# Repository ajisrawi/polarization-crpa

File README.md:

# polarization-crpa: 12-element polarization-diverse GNSS anti-jam array

This project studies a 12-channel GNSS CRPA (controlled reception pattern antenna)
that cancels jammers using **polarization and direction together**. It covers the
full chain:
- signal-level anti-jam simulation,
- antenna design checked with openEMS (FDTD),
- KiCad hardware for the antenna boards,
- schematics for the RF front-end, the RFSoC beamformer and the u-blox ZED-X20P receiver.

## Status (read before using anything here)

| Part | State |
|---|---|
| Anti-jam simulator (STAP, power inversion, MVDR, RF-chain mismatch and equalization) | Working, see below |
| **Antenna element rev C** (air-spaced dual-band stacked patch, 4 probes; [hardware/em](hardware/em)) | **openEMS-simulated:** +4.4 to +5.7 dBic at L5/E5/L2/G2/E6 and +7.8 to +8.1 dBic at L1/E1/B1/G1. Axial ratio 0.5-2.2 dB, except E6/B3 at 3.5 dB. |
| Full 12-element array in openEMS | Running / in progress |
| Rev C KiCad boards | Not yet updated (rev A and rev B boards are in `hardware/antenna*`) |
| Rev C active-element, front-end and DSP schematics | Pass ERC; candidate parts marked VERIFY |
| Built or measured hardware | **None.** Everything here is simulation or design data. |

Rev B (`hardware/antenna_tmm`, compact TMM3 ceramic element) was simulated and **rejected**:
its single resonance gives only about 3 % bandwidth, while the lower GNSS block needs 11 %.
The boards are kept for reference.

> **Disclaimer.** This is research and simulation work, not a validated product.
> - Pinouts, footprints and parts marked VERIFY must be checked against the datasheets.
> - The SMD hybrid land pattern is a placeholder.
> - The element must be prototyped and measured before any production.
>
> **Export control.** GNSS anti-jam / CRPA technology is dual-use and controlled in many
> jurisdictions (for example the Wassenaar Arrangement category 7, US EAR/ITAR). Anyone using,
> modifying or shipping these designs is responsible for complying with the export rules
> that apply to them.

- Hardware: [hardware/README.md](hardware/README.md)
- EM models: [hardware/em/em_element.py](hardware/em/em_element.py) (single element) and
  [hardware/em/em_array.py](hardware/em/em_array.py) (full array)
- `run_hardware_array.py` simulates the array exactly as laid out on the plate.
- To install openEMS for the EM scripts:
  1. Download `openEMS_x64_v0.37.0_msvc.zip` from github.com/thliebig/openEMS-Project.
  2. Extract it to `tools/openEMS/`.
  3. Create the Python environment: `uv venv tools/emvenv --python 3.13`.
  4. Install the bundled wheels: `uv pip install --python tools/emvenv/Scripts/python.exe --no-index --find-links tools/openEMS/openEMS/python openEMS`.

## Anti-jam simulator

A simulator for a 12-channel GNSS CRPA. It cancels jammers using **polarization
and direction together** (space-polarization-time adaptive processing, STAP).
Each run synthesizes the raw IQ samples of all 12 channels, runs the adaptive
beamformer on those samples, and scores the result on the true signal model.

```bash
python run_experiments.py
```

Figures and `results/summary.md` are written to `results/`. A full run takes
several minutes, and most of that time is the Monte Carlo in experiment 3.

## Files

| File | Contents |
|---|---|
| `crpa_model.py` | Antenna/port polarization models, array geometry, wideband signal generation, RF-chain mismatch, FIR channel equalizer |
| `crpa_dsp.py` | Space-time snapshots, covariance, power inversion (blind), MVDR (satellite beams), scoring, sky maps |
| `run_experiments.py` | The three array designs and three experiments |

## Arrays compared (12 RF channels each)

| | Design | Elements |
|---|---|---|
| A | Conventional CRPA | 12 RHCP patches, 4x3 grid, lambda/2 spacing |
| B | Your design | 3 RHCP + 3 LHCP + 3 linear "H" patches (0/60/120 deg) + 3 vertical monopoles, same 4x3 grid |
| C | Dual-pol CRPA | 6 dual-feed patches (centre + ring of 5, radius lambda/2), RHCP and LHCP ports both digitized |

## What the model includes

- **Full polarization.** Every port has a direction-dependent receive vector
  (E_theta, E_phi), and every wave has a Jones vector (RHCP satellites; linear,
  circular or elliptical jammers).
- **Physical element patterns.**
  - A patch's E-plane still radiates at grazing angles and its H-plane does not.
    A linear patch is therefore truly "horizontal" only in its H-plane.
  - RHCP patches lose about 12 dB toward the horizon.
  - Monopoles have a null at zenith and their peak at the horizon.
- **Finite cross-polarization isolation** of every port (25 dB by default).
- **Exact wideband array response.** True time delays across the aperture are
  modelled at 10 MS/s complex baseband around L1.
- **RF-chain mismatch** per channel: gain, phase, about 1 ns of delay spread,
  and filter ripple.
- **Channel equalization.** A 64-tap FIR per channel is fitted to a
  calibration-noise injection.
- **Jammer types:** wideband noise jammers (2-8 MHz), CW, and an RHCP "smart" jammer.
- **Satellite C/N0.** In-band jammer power is treated as extra white noise. The
  reference is 45 dB-Hz at 0 dBic, and the tracking threshold is 28 dB-Hz.

## What the model does NOT include

The following are not modelled, so read the results as a comparison between the
designs, not as absolute hardware predictions:

- mutual coupling between elements,
- platform and ground multipath,
- ADC quantization and AGC,
- satellite code and carrier tracking loops (C/N0 is computed analytically),
- errors in attitude and ephemeris.

## Algorithms

- **Power inversion (PI).** Minimizes the output power with unit gain on one
  RHCP reference channel. It is blind: it needs no satellite directions,
  attitude or antenna calibration.
- **MVDR.** Forms one beam per satellite, with unit gain toward that satellite's
  space-polarization steering vector and minimum output power. It needs a
  calibrated array manifold (residual calibration error is modelled at
  0.2 dB / 2 deg), plus attitude and ephemeris.
- Both run as STAP with 1 or 5 taps per channel. A diagonal loading of
  0.1 x noise is applied.

## RHCP jammer study (`python run_rhcp_jammer.py`)

A SkyShield-type GNSS jammer transmits RHCP. This study tests tilting
elements toward the jammer (`Port.boresight_el_deg` / `boresight_az_deg`).
Results are in `results/rhcp_summary.md`.

- **An LHCP antenna aimed at an RHCP jammer rejects it.** It is
  cross-polarized, so only about -25 dB of leakage gets through.
  - It also still sees the satellites at about -16 dB, so the
    jammer-to-satellite contrast becomes *worse* (-8.7 dB).
  - The same LHCP patch facing zenith has a contrast of +8.7 dB, because a
    patch's polarization turns almost linear near the horizon.
- **Your proposal (LHCP tilted toward the jammer) is the weakest variant of
  your design.** It drops to 6/9 satellites at 90 dB J/N.
- **RHCP reference antennas aimed at the jammer are the strongest variant.**
  They keep 9/9 satellites up to 90 dB J/N with both algorithms.
- **Below about 80 dB J/N, pointing makes no difference.** Every array removes
  one or two RHCP jammers by spatial nulling alone.

## Key findings

The full tables are in `results/summary.md`.

1. **A fixed cross-polarized antenna doesn't work against a strong jammer.**
   An H antenna facing a perfectly vertical 60 dB jammer still leaves +24 dB of
   jammer at the output. The limits are the element's 25 dB cross-pol
   isolation and the antenna's low gain near the horizon. At a 10 deg tilt the
   residual is +36 dB.
2. **Adaptive polarization works at any jammer tilt.** One dual-pol patch with
   two digitized ports pushes the jammer below the noise floor for every tilt
   from 0 to 90 deg. A satellite 3 deg from the jammer keeps 29.5 dB-Hz.
3. **Space-only nulling loses satellites close to a jammer.** The
   conventional 12x RHCP array also removes the jammer, but the satellite
   3 deg away drops to about 10 dB-Hz and is lost.
4. **Your mixed design works.**
   - Full scenario (6 jammers, including an RHCP smart jammer and two jammers
     right next to satellites): it tracks 9/9 satellites with MVDR. The
     12x RHCP array tracks 7/9 and the dual-pol array 9/9.
   - Monte Carlo: it holds all 9 satellites up to 6 jammers, the best of the
     three designs.
5. **Channel matching is the hidden requirement.** With raw, mismatched RF
   chains (about 1 ns delay spread, 0.4 dB ripple), every design collapses
   after about 6 jammers. Your mixed design collapses hardest: it drops to 0
   satellites at 7 jammers. With per-channel FIR equalization from a cal
   injection, the designs still keep 6-7 of 9 satellites at 8 jammers and
   degrade gradually toward the 11-null limit.
6. **Power inversion vs MVDR.** Blind power inversion keeps 5-7 of 9
   satellites in the full scenario. Satellite-steered MVDR keeps 7-9 of 9 and
   adds up to about 10 dB of array gain, but it needs calibration, attitude
   and ephemeris.

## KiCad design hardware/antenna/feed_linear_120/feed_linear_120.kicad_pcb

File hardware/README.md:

# CRPA hardware: 12-element all-band GNSS anti-jam array

KiCad 10 design files for the 12-element polarization-diverse CRPA simulated in the
parent folder. All files are **generated by scripts**, so change the generator scripts
and re-run them rather than editing the boards by hand.

| Status | Board | Files |
|---|---|---|
| Layout done, DRC 0 errors, Gerbers exported | Element feed board, circular (RHCP/LHCP selectable) | `antenna/feed_circular/` |
| Layout done, DRC 0 errors, Gerbers exported | Element feed board, linear | `antenna/feed_linear/` |
| Layout done, DRC 0 errors, Gerbers exported | Lower patch carrier (1164-1300 MHz) | `antenna/patch_lower/` |
| Layout done, DRC 0 errors, Gerbers exported | Upper patch carrier (1559-1610 MHz) | `antenna/patch_upper/` |
| Outline and holes, DXF exported | Aluminium array ground plate | `antenna/array_plate/` |
| Schematic, ERC 0 errors / 0 warnings | 12-channel RF front-end | `rf_frontend/` |
| Schematic, ERC 0 errors / 0 warnings | RFSoC carrier + u-blox ZED-X20P | `dsp_gnss/` |

> **Rev B (compact, Rogers TMM3 elements, 320 x 395 mm array) is in
> [antenna_tmm/](antenna_tmm/README.md) and supersedes the rev A antenna below.**
> The front-end and DSP/GNSS schematics are shared by both revisions.

> **Before ordering anything, read the "Not done yet / must verify" section.** The
> antenna dimensions come from closed-form models and must be tuned in a full-wave EM
> solver. Several part numbers are candidates whose pinouts must be checked.

---

## 1. System architecture

```
 12 antenna elements                     RF front-end (x12)                     RFSoC carrier
 -------------------                     ------------------                     -------------
 3x RHCP   (zenith)  -\                                                         ZU49DR SOM (iWave G42M)
 3x linear (zenith)    >-- SMA --> limiter -> 20dB coupler -> LNA -> BPF ->       RF-ADC x12 @ 2.0 GSPS
 3x monopole (zenith)  |                          ^         gain block -> SMA --> (2nd Nyquist 1.0-2.0 GHz)
 3x LHCP/RHCP (tilted to jammer, el 10 deg) -/     |                                    |
                                                  | cal tone/noise          STAP beamformer in PL
                                     1:12 split <-+---------- SMA <-------- RF-DAC1 (calibration)
                                                                                    |
                                     u-blox ZED-X20P <-- 10 dB pad <-- LPF <-- RF-DAC0 (clean L-band RF)
                                     (all-band GNSS)                     \---- RF-DAC2 -> AJ RF OUT (SMA)
```

- **Direct RF sampling.** The RF-ADCs sample at 2.0 GSPS, so 1.0-2.0 GHz is the
  second Nyquist zone. It contains every GNSS band from 1164 to 1610 MHz with margin, so
  no mixers and no local oscillators are needed.
- **Why the RF-DAC.** The ZED-X20P only accepts RF, so the beamformed signal is
  re-synthesized at L-band by an RF-DAC at about 6.4 GSPS. Commercial anti-jam units feed
  COTS receivers the same way. The few-microsecond latency appears to the receiver as a
  common clock bias and does not affect the position solution.
- **Channel equalization.** RF-DAC1 injects a calibration signal through the 20 dB
  couplers. The FPGA measures every chain and applies per-channel FIR equalizers. The
  simulation showed that without equalization the array collapses after about 6 jammers.

## 2. Antenna element

Air-spaced, dual-band stacked patch, built from three PCBs and nylon M3 standoffs:

```
  upper patch board   FR4 0.8 mm, square patch on the BOTTOM side   81.9 mm   parasitic, 1559-1610 MHz
  ---- 6 mm air (nylon standoffs) ----
  lower patch board   FR4 0.8 mm, square patch on the BOTTOM side  105.5 mm   probe fed, 1164-1300 MHz
  ---- 9 mm air (nylon standoffs), 2 probes of 16 AWG copper wire ----
  feed board          RO4350B 0.762 mm: F.Cu = ground plane, B.Cu = microstrip + printed hybrid + SMA
  ---- >= 6 mm gap to the aluminium plate (keeps the microstrip impedance) ----
  array plate         6061-T6, 3 mm; SMA passes through an 8.4 mm hole
```

| Parameter | Value | Source |
|---|---|---|
| Board size | 124 x 124 mm (element pitch 125 mm) | |
| Probe offset from patch centre | 25.3 mm, at +x and at +y (screen-up) | TL model |
| Probe reactance at 1.23 GHz | about 57 ohm, so C1 and C2 can take ~2.2 pF to cancel it | `design_calc.py` |
| Hybrid | 2-section branch line: Za 115 ohm (0.28 mm), Zb 40 ohm (2.37 mm), Zc 36 ohm (2.77 mm) | optimized over 1164-1610 MHz |
| Hybrid return loss / isolation | >= 22 dB / >= 22.7 dB (ideal lines) | `hybrid_response.png` |
| Hybrid amplitude / phase error | 0.65 dB / 0.2 deg, about 0.65 dB axial ratio | |

### Choosing RHCP or LHCP (feed_circular)

| Polarization | R2 (series, port 1) | R1 (shunt, port 1) | R4 (series, port 4) | R3 (shunt, port 4) |
|---|---|---|---|---|
| **RHCP** | 0 ohm | DNP | DNP | 49.9 ohm |
| **LHCP** | DNP | 49.9 ohm | 0 ohm | DNP |

Use 0603 thin-film resistors. C1 and C2 are the probe-tuning positions: fit 0 ohm until
the element has been measured.

> **Recommendation for the 3 tilted modules:** build them as **RHCP**. On the real
> hardware geometry (`run_hardware_array.py`), tilted LHCP modules lose satellites
> against an 80-90 dB RHCP jammer (power inversion: 2/9 and 0/9 tracked). Tilted RHCP
> modules keep 9/9. The boards support both settings, so this choice costs nothing.

### Linear elements

`feed_linear` is the same stack with a single probe. The E-field is along the probe
axis, which the silkscreen marks. The three H modules are rotated 0, 60 and 120 deg on
the plate. The three vertical elements are 50-52 mm brass rods (6.35 mm diameter) on SMA
bulkheads, a fat monopole for bandwidth. Tune the rod length on a VNA.

### Array plate (`array_plate/array_plate.dxf`, `element_positions.json`)

```
              JAMMER SIDE  (az 0, boresight el 10 deg)
        [L-tilt]        [L-tilt]        [L-tilt]      <- brackets, 80 deg from horizontal
         R  (-125,-125)  H 0deg (0,-125)  V (125,-125)
         V  (-125,0)     R (0,0) REF     H 60deg (125,0)
         H 120deg(-125,125) V (0,125)    R (125,125)
```

The mixed layout means no row or column repeats an element type. The centre RHCP
element is the power-inversion reference. The tilted-module bracket is a 3 mm aluminium
angle bent to 80 deg, with two M4 holes into the plate and the module's four M3 holes on
the tilted face.

## 3. RF front-end (`rf_frontend/`)

| Stage | Candidate part (VERIFY) | Purpose |
|---|---|---|
| Limiter | PIN limiter, about +40 dBm survivable | Survive a close high-power jammer |
| 20 dB coupler | 1.1-1.7 GHz directional coupler | Calibration injection |
| LNA | Infineon BGA855N6 (1164-1615 MHz GNSS LNA) | Sets the noise figure |
| Band-pass | 1150-1620 MHz | Anti-alias for the 2nd Nyquist zone, rejects 900 MHz / 2.4 GHz C2 links |
| Gain block | Mini-Circuits PGA-103+, choke-biased from 5 V | Drives the ADC |
| Cal splitter | 1:4 then 3x 1:4 (spare output terminated) | 12 calibration feeds |

**Rough link budget (estimate, verify with datasheets):** gain about 32 dB, noise
figure about 1.6 dB.
- The noise floor at the ADC is about -141 dBm/Hz, roughly 8 dB above the RF-ADC's own
  noise, so the ADC adds about 0.6 dB.
- With about 6 dB back-off from the ADC's +1 dBm full scale, the largest jammer the chain
  handles is roughly **-40 dBm at each element**.
- A SkyShield-class jammer (100 W, 13 dBi, all power in one GNSS band) gives about
  -53 dBm at 10 km and about -39 dBm at 2 km.
- **Recommended addition:** a 0-31.5 dB digital step attenuator per channel, under AGC
  from the FPGA. It adds about 30 dB of headroom against close-in jammers.

## 4. RFSoC carrier and GNSS receiver (`dsp_gnss/`)

- **SOM:** iWave iW-RainboW-G42M, ZU49DR (16 RF-ADCs at 2.5 GSPS, 16 RF-DACs at
  10 GSPS, 2 x 400-pin board-to-board connectors).
  - The SOM symbol is functional.
  - Every pin must be mapped to the iWave pinout (you need iWave's datasheet and
    carrier design guide).
  - Clocking (RF PLL, SYSREF) must follow iWave's reference carrier.
- **GNSS receiver:** u-blox **ZED-X20P**, all-band L1/L2/L5/L6 (GPS, Galileo, GLONASS,
  BeiDou, QZSS, NavIC). It uses KiCad's reviewed `RF_GPS:ZED-F9P` symbol and
  `RF_GPS:ublox_ZED` footprint, because u-blox states the X20 is pin-to-pin compatible
  with the F9.
  - **Verify every pin against the ZED-X20P datasheet.** SparkFun reports at least one
    pin whose function changed.
  - VCC_RF and the antenna-supervisor pins are left unconnected: the RF comes from the
    DAC, so there is no active antenna to power.
- **Interfaces:**
  - SOM UART to ZED UART1.
  - ZED TIMEPULSE to the SOM's PPS input and a PPS SMA.
  - USB-C for u-center.
  - UART2/I2C header for RTCM corrections.
  - SMA outputs: AJ RF OUT, CAL OUT and 10 MHz REF OUT.
- **Power:** 12 V in. A buck converter makes 5 V for the front-end and the LDO, and a
  low-noise LDO makes 3.3 V for the GNSS receiver and the clock.

## 5. Not done yet / must verify

1. **EM simulation of the element (required).** Model the patch stack, probes and
   hybrid in openEMS, CST or HFSS. Tune h1, h2, patch sizes, probe offset, C1/C2 and the
   hybrid lengths (T-junction parasitics are not modelled) until:
   - |S11| < -10 dB in both bands,
   - axial ratio < 3 dB at boresight,
   - gain at 10 deg elevation is acceptable.

   Then change `design_params.json` and re-run `gen_boards.py`.
2. **Mutual coupling and pitch.** The 125 mm pitch is forced by the 105 mm air-patch
   size. It is 0.66 lambda at L1, so the array has grating lobes. Simulate the full
   array in EM, and consider dielectric loading to shrink the elements.
3. **Part numbers marked VERIFY** in the schematics: pinouts, footprints, availability,
   and export classification.
4. **PCB layout** of the front-end and carrier. Both need controlled-impedance stack-ups
   and phase-matched channel routing.
5. **Firmware:**
   - RFSoC tile configuration,
   - channel equalizer,
   - STAP weights (power inversion first, MVDR later; port `crpa_dsp.py`),
   - DAC re-synthesis,
   - AGC.
6. **Export control.** CRPA and anti-jam hardware is controlled in many jurisdictions
   (for example the US EAR/ITAR and the Wassenaar dual-use list). Check before
   manufacturing or shipping.

## 6. How to rebuild

```bash
python hardware/antenna/design_calc.py
"C:/Program Files/KiCad/10.0/bin/python.exe" hardware/antenna/gen_boards.py
powershell -File hardware/tools/check_boards.ps1 hardware/antenna
powershell -File hardware/tools/export_fab.ps1 hardware/antenna
powershell -File hardware/tools/check_schematics.ps1
python run_hardware_array.py
```

The two board scripts do the following:
- `check_boards.ps1` fills the copper zones and runs DRC; KiCad's zone filler crashes
  when run headless from Python, so it is done through kicad-cli.
- `export_fab.ps1` writes, for each board, Gerbers, an Excellon drill file, a
  pick-and-place file, renders, and a zip in `<board>/`.

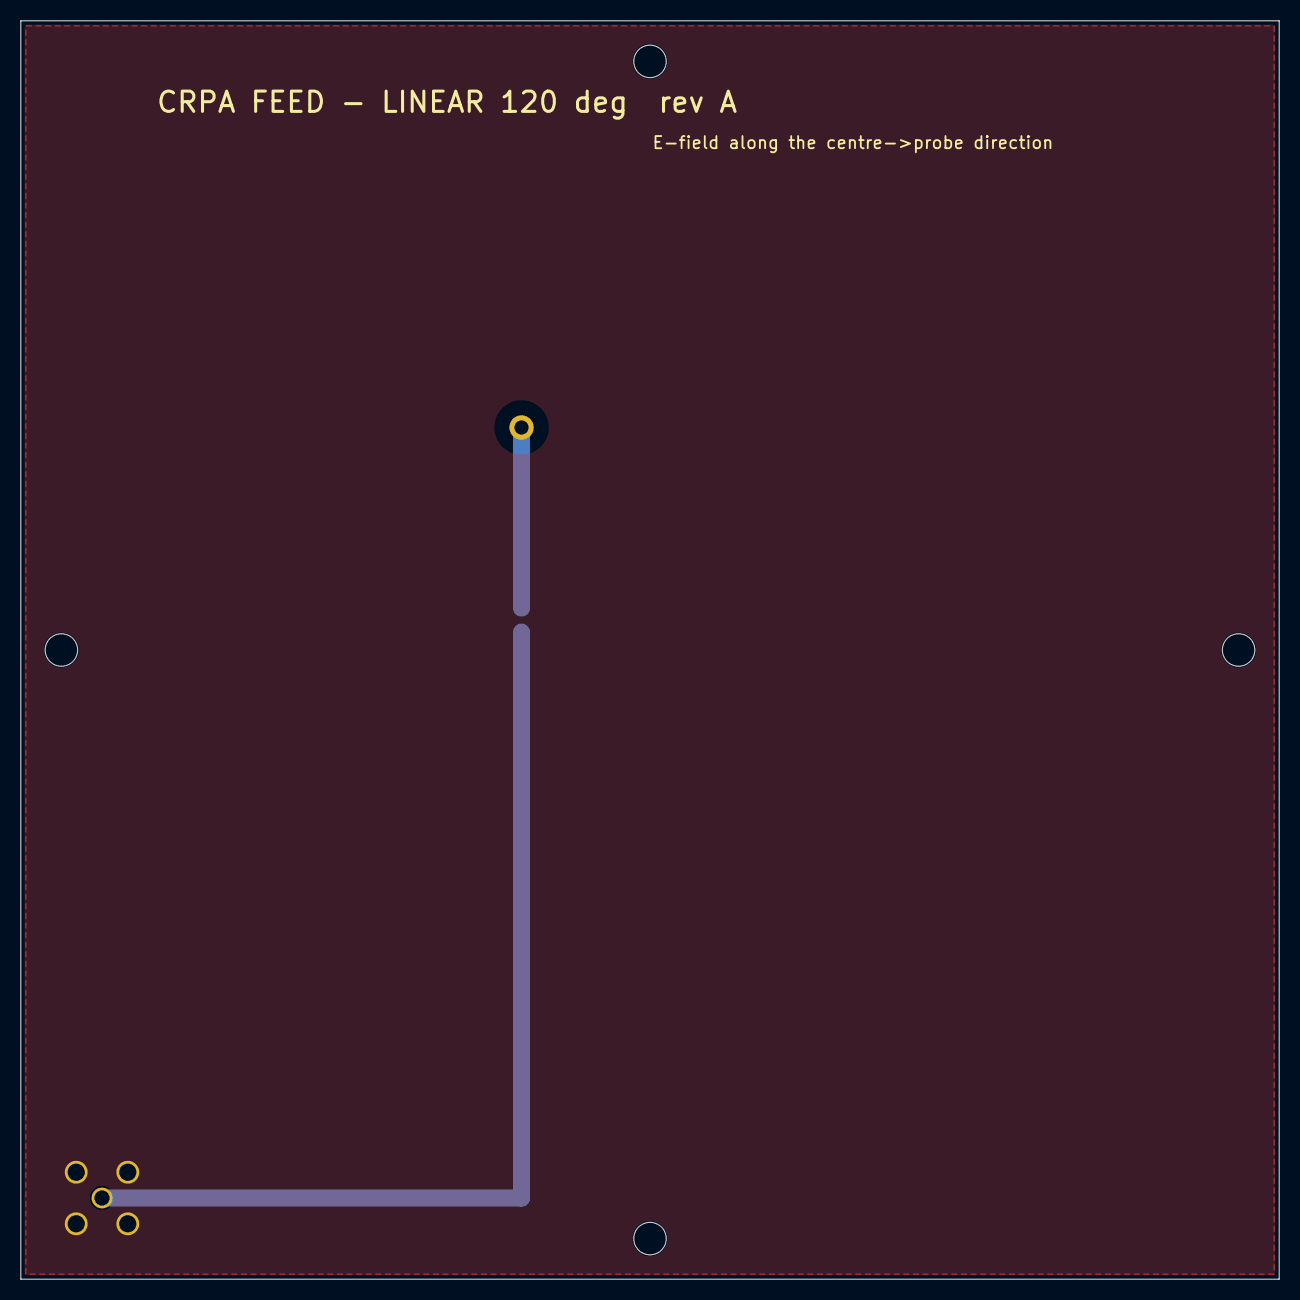
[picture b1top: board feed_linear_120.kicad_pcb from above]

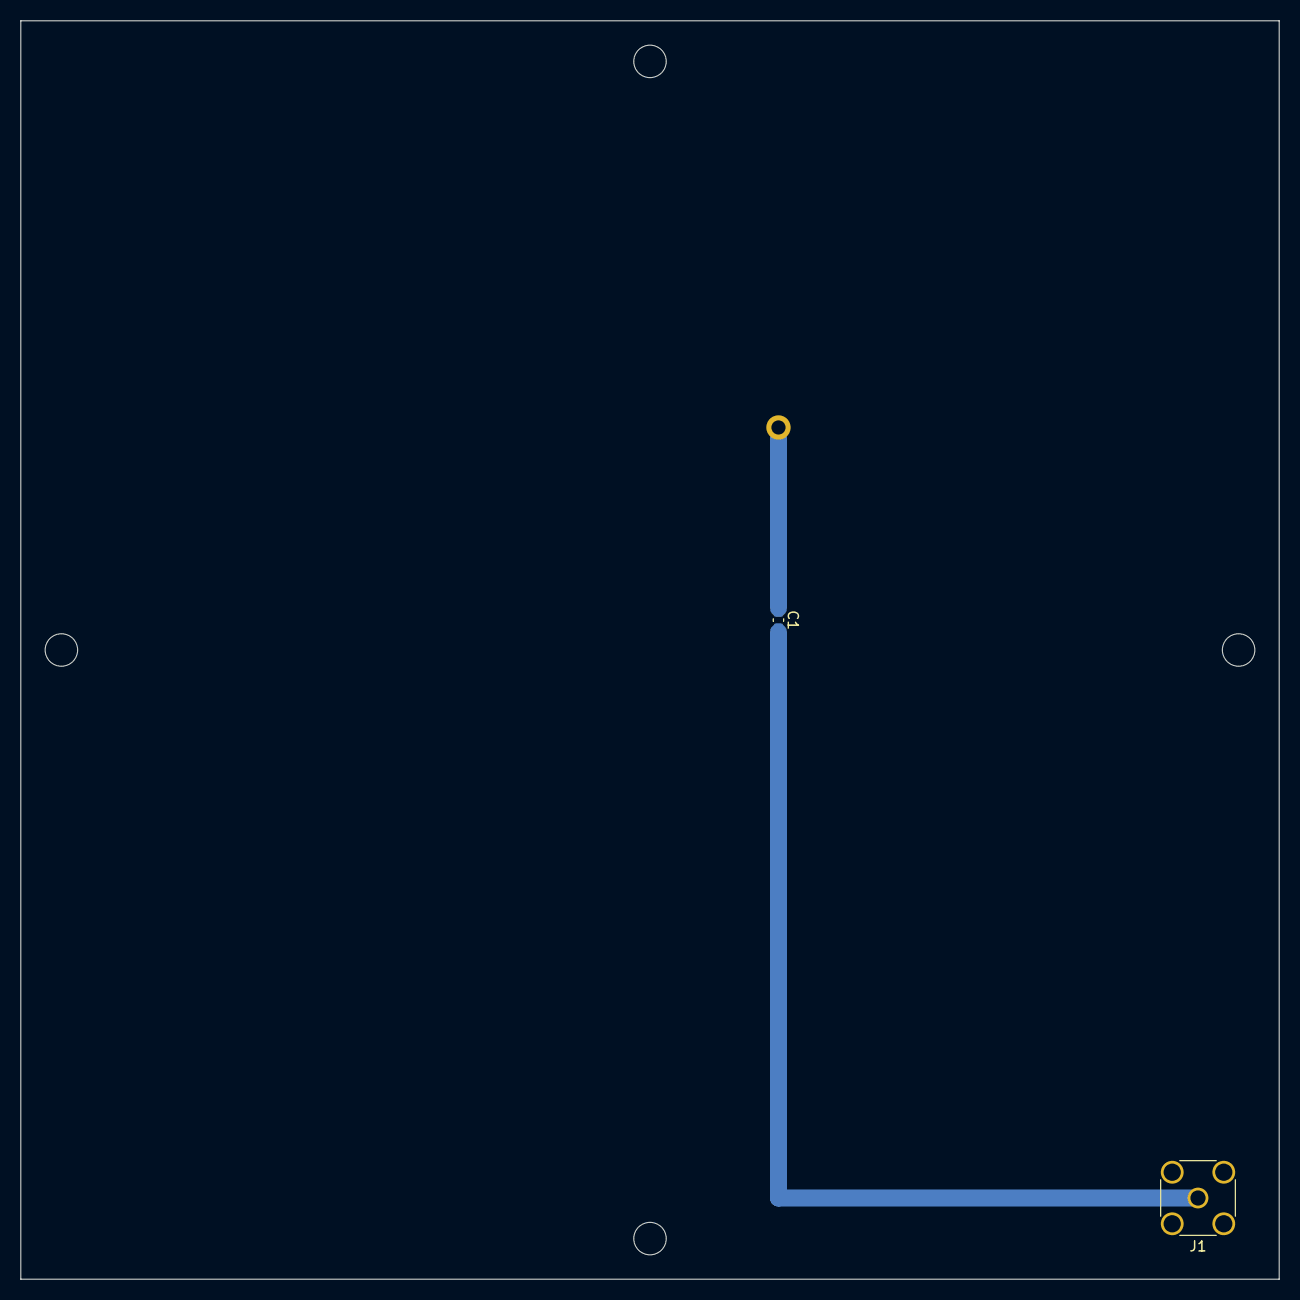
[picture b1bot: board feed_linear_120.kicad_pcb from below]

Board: 2 copper layers, 124.0 x 124.0 mm, 7 parts (2 on the bottom side), 2 nets.

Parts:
C1: 0R / ~2.2pF probe tune; C_0603_1608Metric
H1, H2, H3, H4: M3 nylon standoff; MountingHole_3.2mm_M3
J1: SMA vertical (Amphenol 132134); SMA_Amphenol_132134_Vertical
P1: probe

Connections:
PROBE: C1.1, P1.1
RF_OUT: C1.2, J1.1

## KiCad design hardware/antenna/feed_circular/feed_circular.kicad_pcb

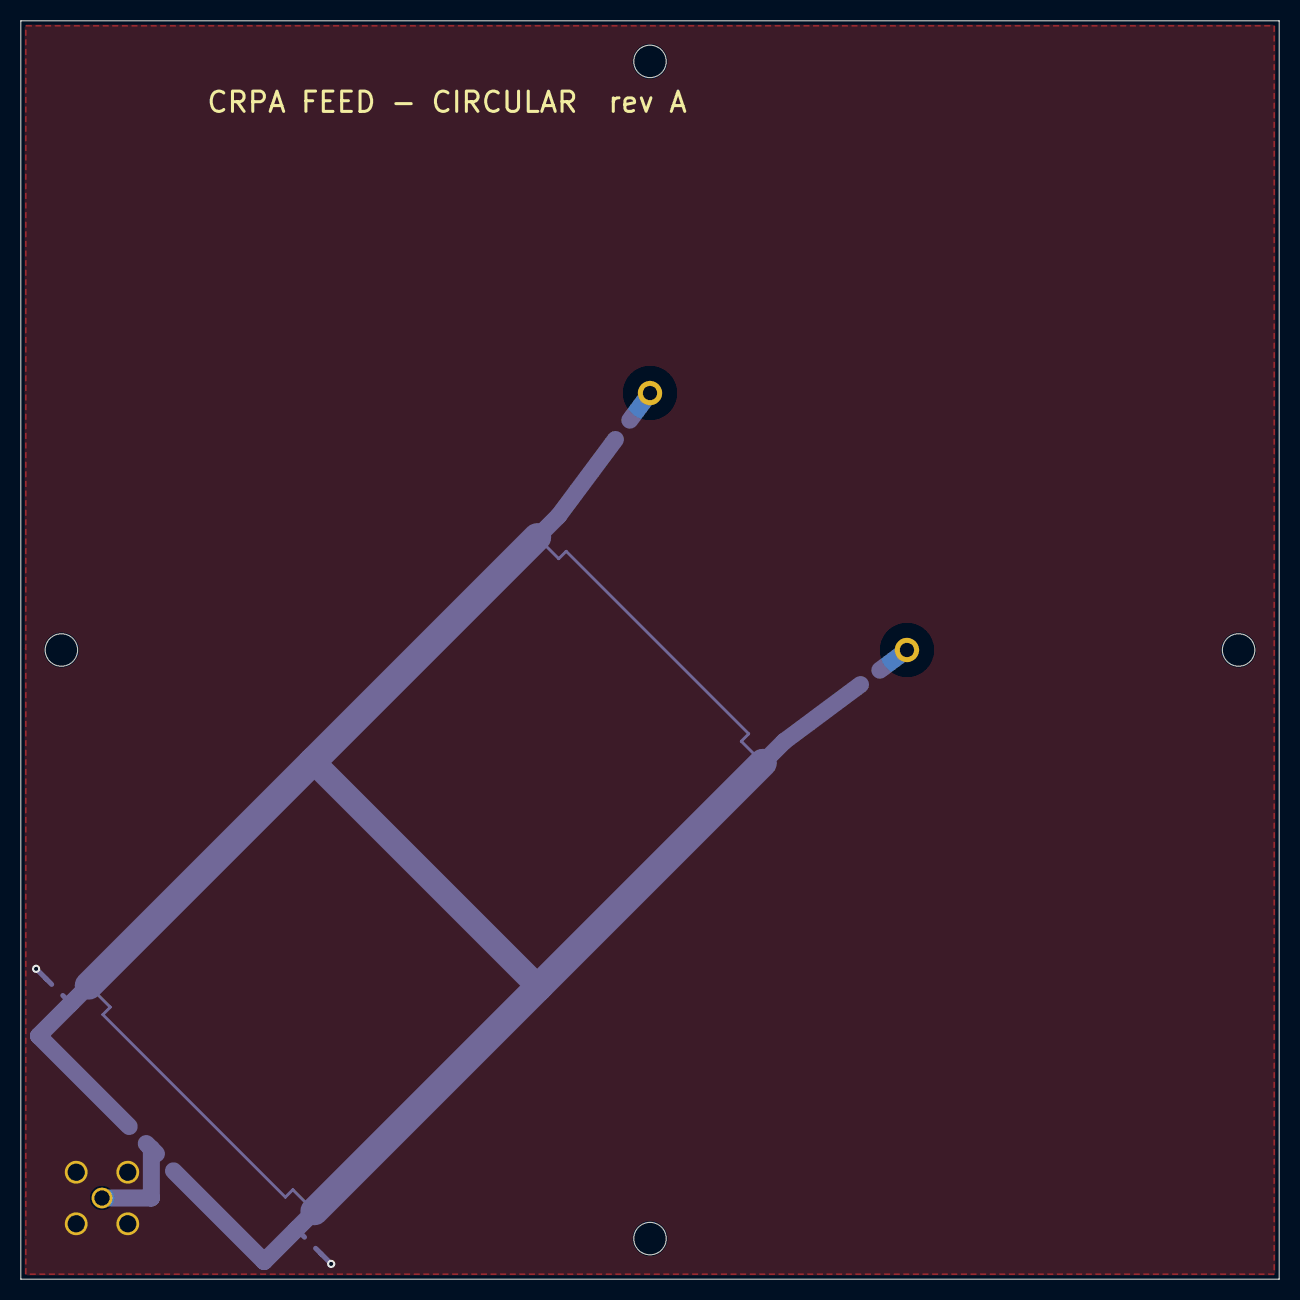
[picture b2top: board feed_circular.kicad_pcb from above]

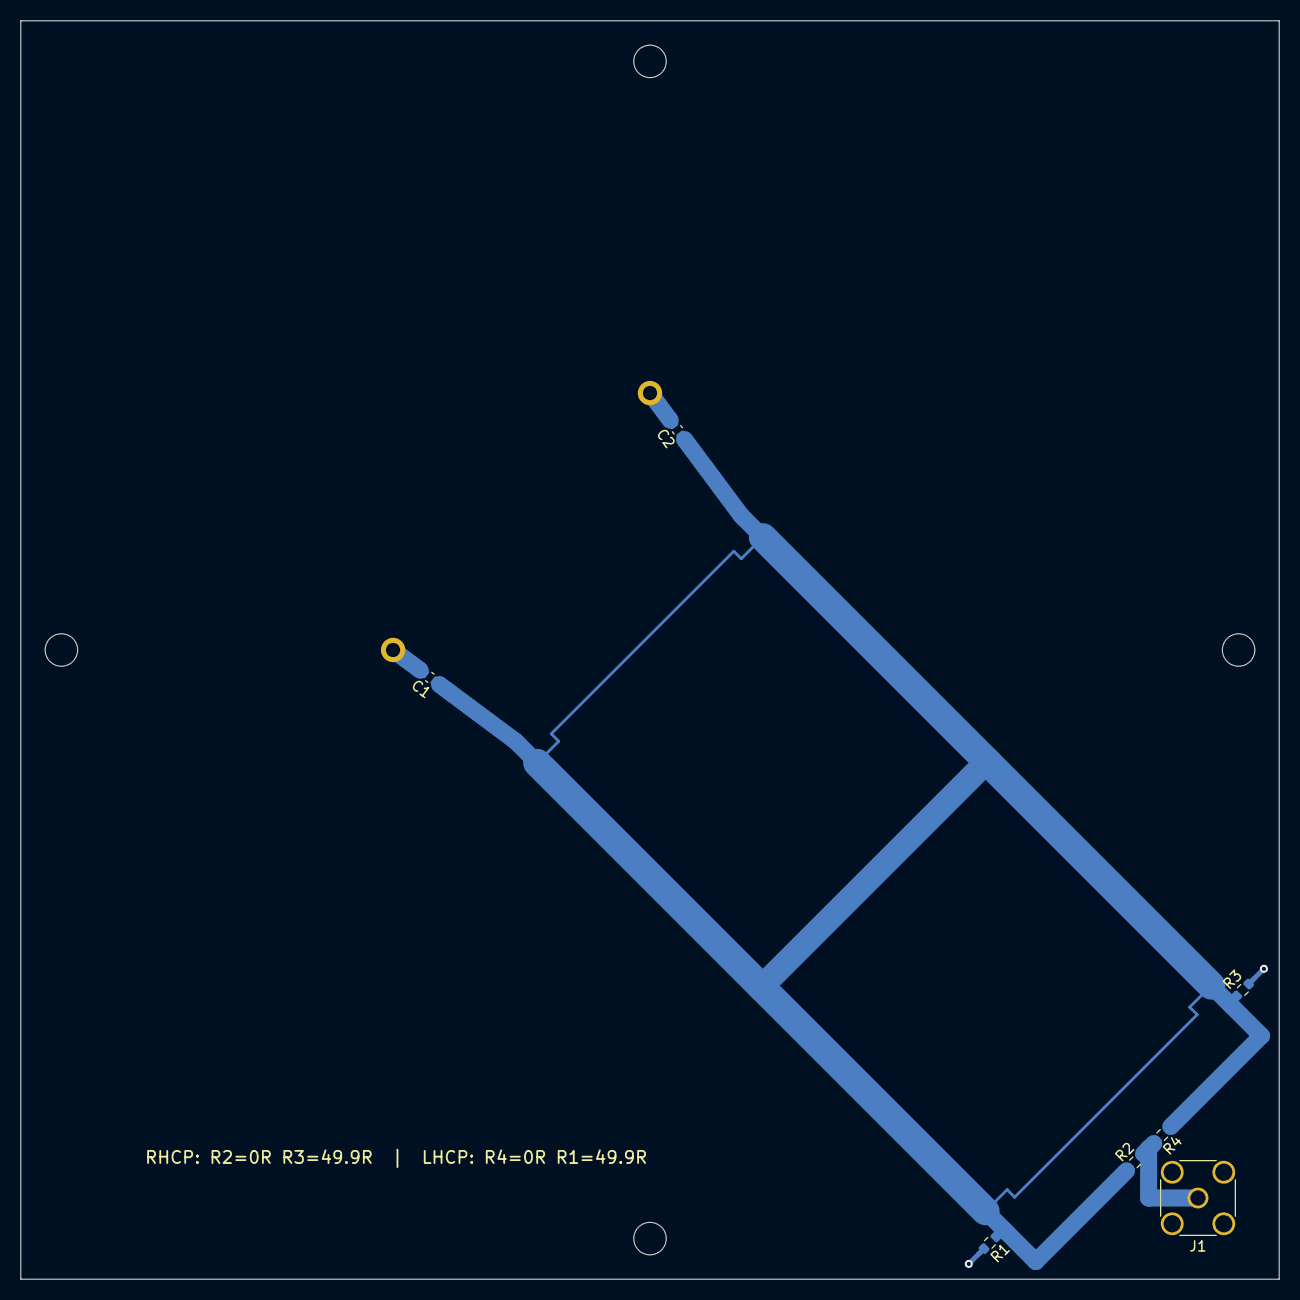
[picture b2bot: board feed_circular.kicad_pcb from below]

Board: 2 copper layers, 124.0 x 124.0 mm, 13 parts (7 on the bottom side), 5 nets.

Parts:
C1, C2: 0R / ~2.2pF probe tune; C_0603_1608Metric
H1, H2, H3, H4: M3 nylon standoff; MountingHole_3.2mm_M3
J1: SMA vertical (Amphenol 132134); SMA_Amphenol_132134_Vertical
P1, P2: probe
R1: 49.9R if RHCP not used, else DNP; R_0603_1608Metric
R2: 0R for RHCP, else DNP; R_0603_1608Metric
R3: 49.9R if LHCP not used, else DNP; R_0603_1608Metric
R4: 0R for LHCP, else DNP; R_0603_1608Metric

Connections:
GND: J1.2, R1.2, R3.2
HYB_T: C1.1, C2.1, R1.1, R2.1, R3.1, R4.1
PROBE_X: C1.2, P1.1
PROBE_Y: C2.2, P2.1
RF_OUT: J1.1, R2.2, R4.2
